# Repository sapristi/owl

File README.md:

# The Owl

The Owl is a 36-key (diodeless!), MX-spaced, wireless keyboard.

It was forked from the [rae-dux](https://github.com/andrewjrae/rae-dux) (itself inspired by the [Architeuthis Dux](https://github.com/tapioki/cephalopoda/tree/main/Architeuthis%20dux) ).

The main difference with the rae-dux is that MX-spacing is used for the keys. This keyboard is also designed with top and bottom plates, so as to protect the MCU and the battery. The mounting holes will fit m3 screws / standoffs.

**Note**: the top-plate doesn't need the mounting holes, so you could remove them from the kicad files.

## Art

The art for the keyboard is from vecteezy.com:
 - top was adapted from https://www.vecteezy.com/vector-art/2531138-black-and-white-line-art-of-owl
 - bottom was adapted from https://www.vecteezy.com/vector-art/3378572-barn-owl-flying-over-black-background

## Firmware

Since the keyboard is the same as the rae-dux, you can use the rae-dux firmware for it, see e.g.
- [my rae-dux ZMK config](https://github.com/sapristi/zmk-config-rae-dux)
- the original [rae-dux ZMK shield](https://github.com/andrewjrae/zmk-config/tree/development/config/boards/shields/rae_dux) (note: this is configured to use an older zmk version, with some bugs on mod-tap)

## Build Guide

Checkout the build-guide for the [rae-dux](./build_guide/index.md). The main difference is that the MCUs are mounted on the bottom of the PCBs.

A small thing you can change is also to put power switche on different sides of the pcb, so that both are in the same position for on-off.

## Important Notes
- **Wireless only**, the 36-key diodeless approach uses the P0 pin which is usually dedicated to TRRS
- There is only one MCU footprint, so **one controller has to be flipped**
- If you want to skip out on the switch, there is no jumper to use the JST
  connector, so you'll have to bodge a wire somewhere, or try shorting the
  switch footprint.

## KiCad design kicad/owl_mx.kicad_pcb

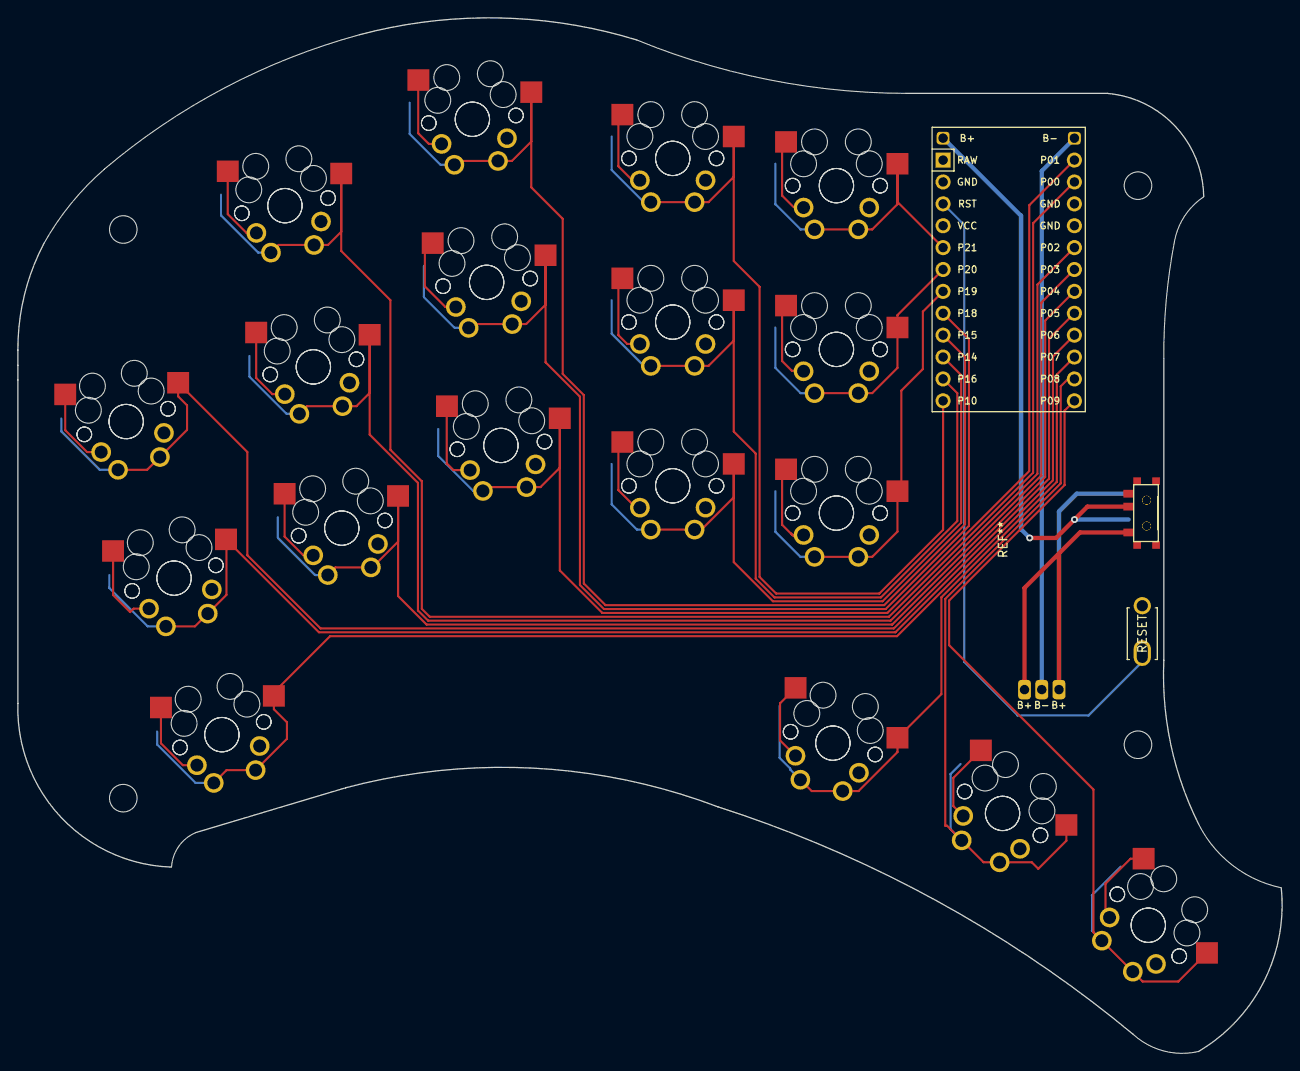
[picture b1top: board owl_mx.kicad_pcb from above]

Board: 2 copper layers, 146.7 x 120.2 mm, 44 parts (0 on the bottom side), 22 nets.

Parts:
B1: ResetSW
MCU1: ProMicro
MOUNTING_PAD1, MOUNTING_PAD2, MOUNTING_PAD3, MOUNTING_PAD4: SMDPad
S1, S2, S3, S4, S5, S6, S7, S8, S9, S10, S11, S12, S13, S14, S15, S16, S17, S18, S19, S20, S21, S22, S23, S24, S25, S26, S27, S28, S29, S30, S31, S32, S33, S34, S35, S36: MX
T1, T2: SPDT_C128955

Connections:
Bplus: MCU1.25, T1.2, T2.2
Braw: T1.1, T2.1
GND: B1.2, MCU1.2, MCU1.15, MCU1.16, S1.2, S2.2, S3.2, S4.2, S5.2, S6.2, S7.2, S8.2, S9.2, S10.2, S11.2, S12.2, S13.2, S14.2, S15.2, S16.2, S17.2, S18.2, S19.2, S20.2, S21.2, S22.2, S23.2, S24.2, S25.2, S26.2, S27.2, S28.2, S29.2, S30.2, S31.2, S32.2, S33.2, S34.2, S35.2, S36.2
P0: MCU1.14, S11.1, S12.1
P1: MCU1.13, S13.1, S14.1
P2: MCU1.17, S9.1, S10.1
P3: MCU1.18, S7.1, S8.1
P4: MCU1.19, S5.1, S6.1
P5: MCU1.20, S3.1, S4.1
P6: MCU1.21, S1.1, S2.1
P7: MCU1.22, S31.1, S32.1
P8: MCU1.23, S33.1, S34.1
P9: MCU1.24, S35.1, S36.1
P10: MCU1.12, S23.1, S24.1
P14: MCU1.10, S19.1, S20.1
P15: MCU1.9, S17.1, S18.1
P16: MCU1.11, S21.1, S22.1
P18: MCU1.8, S15.1, S16.1
P19: MCU1.7, S25.1, S26.1
P20: MCU1.6, S27.1, S28.1
P21: MCU1.5, S29.1, S30.1
RST: B1.1, MCU1.3

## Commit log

2022-11-16 readme
2022-11-20 restore ergogen yaml config
2022-11-22 in progress
2023-01-01 gerbers and readme
2023-01-01 image
2023-01-14 readme: notes about zmk
2023-09-10 build guide copy
2023-12-20 bottom gerbers
